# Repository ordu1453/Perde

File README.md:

# Perde

## Repository Layout

| Directory | Contents |
|---|---|
| `hw/` | Hardware design sources (KiCad projects) |
| `fw/` | Firmware sources |
| `mech/` | Mechanical design sources |

## Hardware

The PCB design lives in [`hw/main-board`](hw/main-board), a KiCad 10 project consisting of the schematic (`main-board.kicad_sch`), the board layout (`main-board.kicad_pcb`), and the build configuration for [KiBot](https://github.com/INTI-CMNB/KiBot) (`main-board.kibot.yaml`).

### Continuous Integration / Continuous Delivery

Every change to the hardware design is automatically validated and built by GitHub Actions. The pipeline is implemented with KiBot, executed inside the official `kicad10_auto` / `kicad10_auto_full` container images (KiCad 10), and performs visual revision comparison via [KiDiff](https://github.com/INTI-CMNB/KiDiff), exposed through KiBot's `diff` output. Workflow definitions reside under [`.github/workflows`](.github/workflows).

#### `kicad-ci.yml` — Continuous Integration

Triggered on every push and pull request affecting `hw/main-board/**`. The workflow consists of the following jobs:

| Job | Description |
|---|---|
| **ERC / DRC + docs** | Executes the Electrical Rules Check and Design Rules Check preflights, and generates PDF exports of the schematic and PCB layout. |
| **Gerbers / drill / BOM / STEP** | Produces Gerber and drill files for JLCPCB and PCBWay using KiBot's built-in per-manufacturer templates, each in its own directory with its own ZIP archive (JLCPCB's additionally includes an LCSC-formatted BOM and pick-and-place file); a manufacturer-neutral Bill of Materials (HTML and CSV), a pick-and-place file, and a STEP 3D model are generated separately. |
| **3D renders** | Renders top and bottom views of the assembled board. |
| **Visual diff (KiDiff)** | Generates a red/green visual comparison of the PCB and schematic against a prior revision — the pull request base branch when run on a pull request, or the preceding commit when run on a direct push. |
| **Publish latest build** | Consolidates the outputs of the jobs above, regenerates an interactive KiCanvas schematic/PCB viewer and a KiBot `navigate_results` index over the merged tree, and publishes the result to the `gh-pages` branch under `/latest/`, providing a persistent, browsable link to the most recent build of `main`. |

As the hardware design is presently at an early stage, the pipeline defaults to not failing on design-rule violations: KiBot is invoked with `-D` (`--dont-stop`), which always applies, and each step's `continue-on-error` is controlled by the **`KICAD_CI_STRICT`** repository variable (*Settings → Secrets and variables → Actions → Variables*):

- Unset, or any value other than `true` (default) — lenient: a real ERC/DRC/output failure is still reported in the uploaded artifacts, but does not fail the job, so an early-stage or placeholder design doesn't block CI.
- `true` — strict: a real failure fails the job for real, and any job depending on it (fabrication, renders, publish-latest) is skipped, exactly as with any other genuine CI failure.

Setting `KICAD_CI_STRICT=true` once the design is no longer a placeholder is recommended so a broken board or schematic is reflected honestly in the pipeline's status.

#### `kicad-release.yml` — Release Packaging

Triggered by pushing a tag matching the pattern `vX.Y.Z`. Builds the complete set of documentation, fabrication, assembly, and 3D outputs, and attaches the resulting package to a corresponding GitHub Release. A manual invocation (`workflow_dispatch`) performs the build step only, as no tag is available to publish a release against.

#### Build Outputs

Generated files are retained as downloadable artifacts on each workflow run. In addition, the latest successful build of `main` is published at:

<https://ordu1453.github.io/Perde/latest/>

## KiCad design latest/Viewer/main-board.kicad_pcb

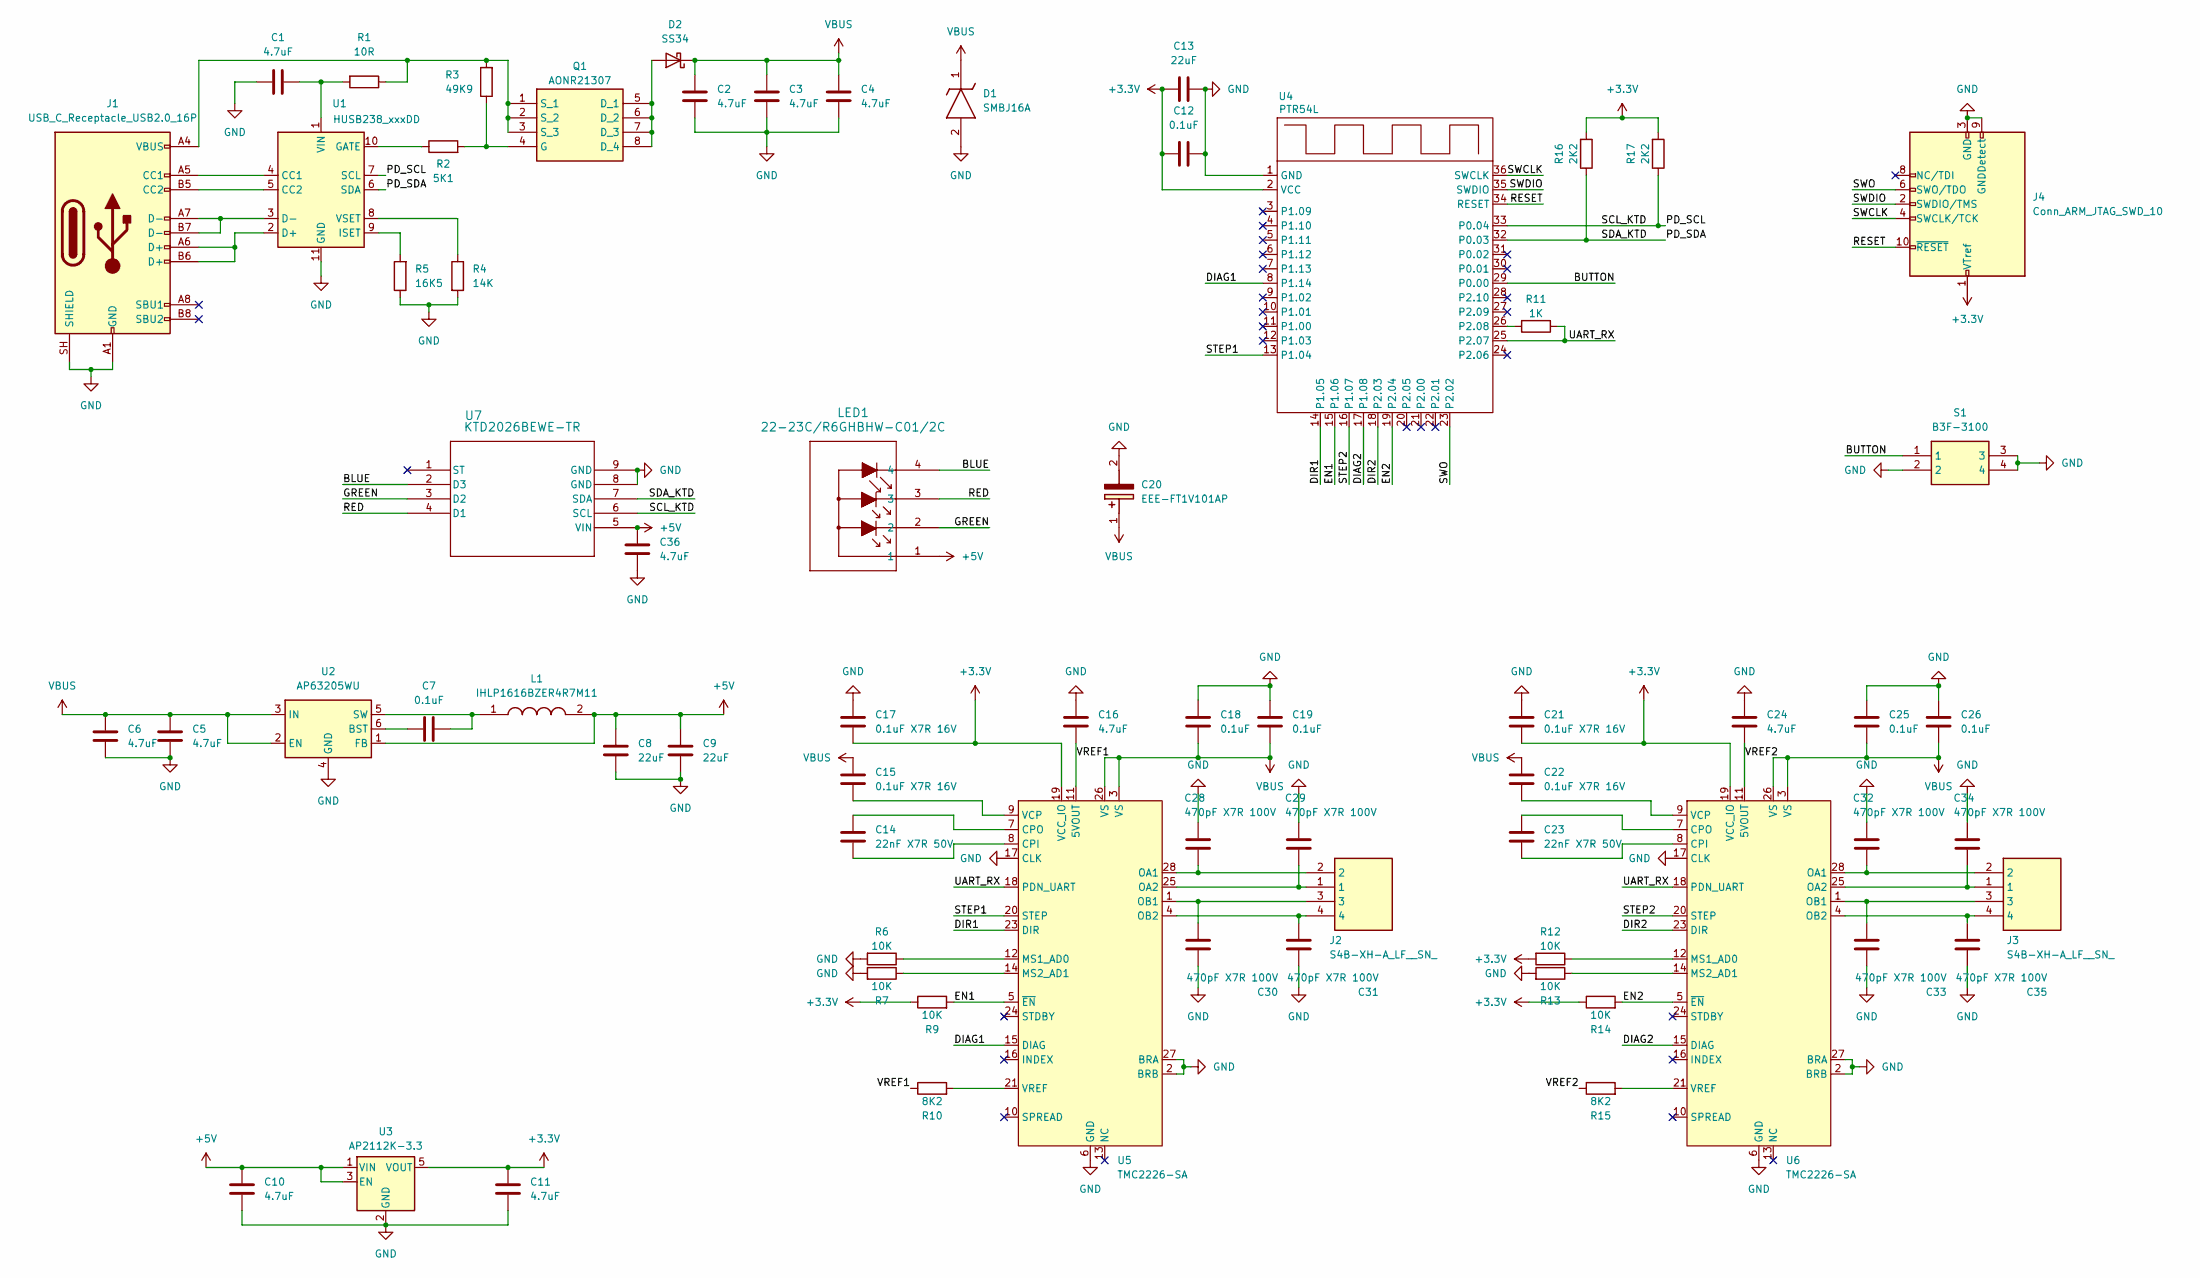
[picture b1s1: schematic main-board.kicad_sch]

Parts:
C1, C2, C3, C4, C5, C6, C10, C11, C16, C24, C36: 4.7uF; C_0805_2012Metric_Pad1.18x1.45mm_HandSolder
C7, C12, C18, C19, C25, C26: 0.1uF; C_0805_2012Metric_Pad1.18x1.45mm_HandSolder
C8, C9, C13: 22uF; C_0603_1608Metric_Pad1.08x0.95mm_HandSolder
C14, C23: 22nF X7R 50V; C_0603_1608Metric_Pad1.08x0.95mm_HandSolder
C15, C17, C21, C22: 0.1uF X7R 16V; C_0603_1608Metric_Pad1.08x0.95mm_HandSolder
C20: EEE-FT1V101AP; EEE1AA101SP; Manufacturer_Part_Number EEE-FT1V101AP; Mouser Part Number 667-EEE-FT1V101AP
C28, C29, C30, C31, C32, C33, C34, C35: 470pF X7R 100V; C_0805_2012Metric_Pad1.18x1.45mm_HandSolder
D1: SMBJ16A; DIOM5436X261N; Manufacturer_Part_Number SMBJ16A; Mouser Part Number 576-SMBJ16A
D2: SS34; D_SMA
J1: USB_C_Receptacle_USB2.0_16P; USB_C_Receptacle_Palconn_UTC16-G
J2, J3: S4B-XH-A_LF__SN_; S4BXHALFSN; Manufacturer_Part_Number S4B-XH-A(LF)(SN); Mouser Part Number N/A
J4: Conn_ARM_JTAG_SWD_10; PinHeader_2x05_P1.27mm_Vertical_SMD
L1: IHLP1616BZER4R7M11; INDPM4441X200N; Manufacturer_Part_Number IHLP1616BZER4R7M11; Mouser Part Number 70-IHLP1616BZER4R7M1
LED1: 22-23C/R6GHBHW-C01/2C; 22-23C_EVE
Q1: AONR21307; DFN_3X3_EP; Manufacturer_Part_Number AONR21307
R1: 10R; R_0805_2012Metric_Pad1.20x1.40mm_HandSolder
R2: 5K1; R_0805_2012Metric_Pad1.20x1.40mm_HandSolder
R3: 49K9; R_0805_2012Metric_Pad1.20x1.40mm_HandSolder
R4: 14K; R_0603_1608Metric_Pad0.98x0.95mm_HandSolder
R5: 16K5; R_0603_1608Metric_Pad0.98x0.95mm_HandSolder
R6, R7, R9, R12, R13, R14: 10K; R_0603_1608Metric_Pad0.98x0.95mm_HandSolder
R10, R15: 8K2; R_0603_1608Metric_Pad0.98x0.95mm_HandSolder
R11: 1K; R_0603_1608Metric_Pad0.98x0.95mm_HandSolder
R16, R17: 2K2; R_0603_1608Metric_Pad0.98x0.95mm_HandSolder
S1: B3F-3100; B3F3100; Manufacturer_Part_Number B3F-3100; Mouser Part Number 653-B3F-3100
U1: HUSB238_xxxDD; WDFN-10-1EP_3x3mm_P0.5mm_EP1.8x2.5mm
U2: AP63205WU; TSOT-23-6
U3: AP2112K-3.3; SOT-23-5
U4: PTR54L; PTR54L15
U5, U6: TMC2226-SA; HTSSOP-28-1EP_4.4x9.7mm_P0.65mm_EP2.75x6.2mm_ThermalVias
U7: KTD2026BEWE-TR; UTDFN8_1P5X1P5_KIN

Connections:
+3.3V: C11.1, C12.2, C13.2, C17.2, C21.2, J4.1 (VTref), R9.1, R12.2, R14.1, R16.2, R17.2, U3.5 (VOUT), U4.2 (VCC), U5.19 (VCC_IO), U6.19 (VCC_IO)
+5V: C8.2, C9.2, C10.1, C36.1, L1.2, LED1.1, U2.1 (FB), U3.1 (VIN), U3.3 (EN), U7.5 (VIN)
/BLUE: LED1.4, U7.2 (D3)
/BUTTON: S1.1, U4.29 (P0.00)
/DIAG1: U4.8 (P1.14), U5.15 (DIAG)
/DIAG2: U4.17 (P1.08), U6.15 (DIAG)
/DIR1: U4.14 (P1.05), U5.23 (DIR)
/DIR2: U4.18 (P2.03), U6.23 (DIR)
/EN1: R9.2, U4.15 (P1.06), U5.5 (~EN)
/EN2: R14.2, U4.19 (P2.04), U6.5 (~EN)
/GREEN: LED1.2, U7.3 (D2)
/PD_SCL: R17.1, U1.7 (SCL), U4.33 (P0.04), U7.6 (SCL)
/PD_SDA: R16.1, U1.6 (SDA), U4.32 (P0.03), U7.7 (SDA)
/RED: LED1.3, U7.4 (D1)
/RESET: J4.10 (~RESET), U4.34 (RESET)
/STEP1: U4.13 (P1.04), U5.20 (STEP)
/STEP2: U4.16 (P1.07), U6.20 (STEP)
/SWCLK: J4.4 (SWCLK/TCK), U4.36 (SWCLK)
/SWDIO: J4.2 (SWDIO/TMS), U4.35 (SWDIO)
/SWO: J4.6 (SWO/TDO), U4.23 (P2.02)
/UART_RX: R11.1, U4.25 (P2.07), U5.18 (PDN_UART), U6.18 (PDN_UART)
/VREF1: C16.2, R10.1, U5.11 (5VOUT)
/VREF2: C24.2, R15.1, U6.11 (5VOUT)
GND: C1.1, C2.2, C3.2, C4.2, C5.2, C6.2, C8.1, C9.1, C10.2, C11.2, C12.1, C13.1, C16.1, C17.1, C18.1, C19.1, C20.2 (-), C21.1, C24.1, C25.1, C26.1, C28.1, C29.1, C30.1, C31.1, C32.1, C33.1, C34.1, C35.1, C36.2, D1.2 (A), J1.A1 (GND), J1.A12 (GND), J1.B1 (GND), J1.B12 (GND), J1.SH (SHIELD), J4.3 (GND), J4.5 (GND), J4.9 (GNDDetect), R4.2, R5.1, R6.2, R7.2, R13.2, S1.2, S1.3, S1.4, U1.11 (GND), U2.4 (GND), U3.2 (GND), U4.1 (GND), U5.2 (BRB), U5.6 (GND), U5.17 (CLK), U5.22 (GND), U5.27 (BRA), U5.29 (GND), U6.2 (BRB), U6.6 (GND), U6.17 (CLK), U6.22 (GND), U6.27 (BRA), U6.29 (GND), U7.8 (GND), U7.9 (GND)
unnamed: D2.2 (A), Q1.5 (D_1), Q1.6 (D_2), Q1.7 (D_3), Q1.8 (D_4)
unnamed: J1.A5 (CC1), U1.4 (CC1)
unnamed: J1.B5 (CC2), U1.5 (CC2)
unnamed: Q1.4 (G), R2.2, R3.1
unnamed: J1.A4 (VBUS), J1.A9 (VBUS), J1.B4 (VBUS), J1.B9 (VBUS), Q1.1 (S_1), Q1.2 (S_2), Q1.3 (S_3), R1.1, R3.2
unnamed: J1.A6 (D+), J1.B6 (D+), U1.2 (D+)
unnamed: J1.A7 (D-), J1.B7 (D-), U1.3 (D-)
unnamed: R2.1, U1.10 (GATE)
unnamed: R5.2, U1.9 (ISET)
unnamed: C1.2, R1.2, U1.1 (VIN)
unnamed: R4.1, U1.8 (VSET)
unnamed: C7.1, U2.6 (BST)
unnamed: C7.2, L1.1, U2.5 (SW)
unnamed: R11.2, U4.26 (P2.08)
unnamed: C14.1, U5.8 (CPI)
unnamed: C14.2, U5.7 (CPO)
unnamed: R6.1, U5.12 (MS1_AD0)
unnamed: R7.1, U5.14 (MS2_AD1)
unnamed: C28.2, J2.2, U5.28 (OA1)
unnamed: C29.2, J2.1, U5.25 (OA2)
unnamed: C30.2, J2.3, U5.1 (OB1)
unnamed: C31.2, J2.4, U5.4 (OB2)
unnamed: C15.2, U5.9 (VCP)
unnamed: R10.2, U5.21 (VREF)
unnamed: C23.1, U6.8 (CPI)
unnamed: C23.2, U6.7 (CPO)
unnamed: R12.1, U6.12 (MS1_AD0)
unnamed: R13.1, U6.14 (MS2_AD1)
unnamed: C32.2, J3.2, U6.28 (OA1)
unnamed: C34.2, J3.1, U6.25 (OA2)
unnamed: C33.2, J3.3, U6.1 (OB1)
unnamed: C35.2, J3.4, U6.4 (OB2)
unnamed: C22.2, U6.9 (VCP)
unnamed: R15.2, U6.21 (VREF)
VBUS: C2.1, C3.1, C4.1, C5.1, C6.1, C15.1, C18.2, C19.2, C20.1 (+), C22.1, C25.2, C26.2, D1.1 (K), D2.1 (K), U2.2 (EN), U2.3 (IN), U5.3 (VS), U5.26 (VS), U6.3 (VS), U6.26 (VS)

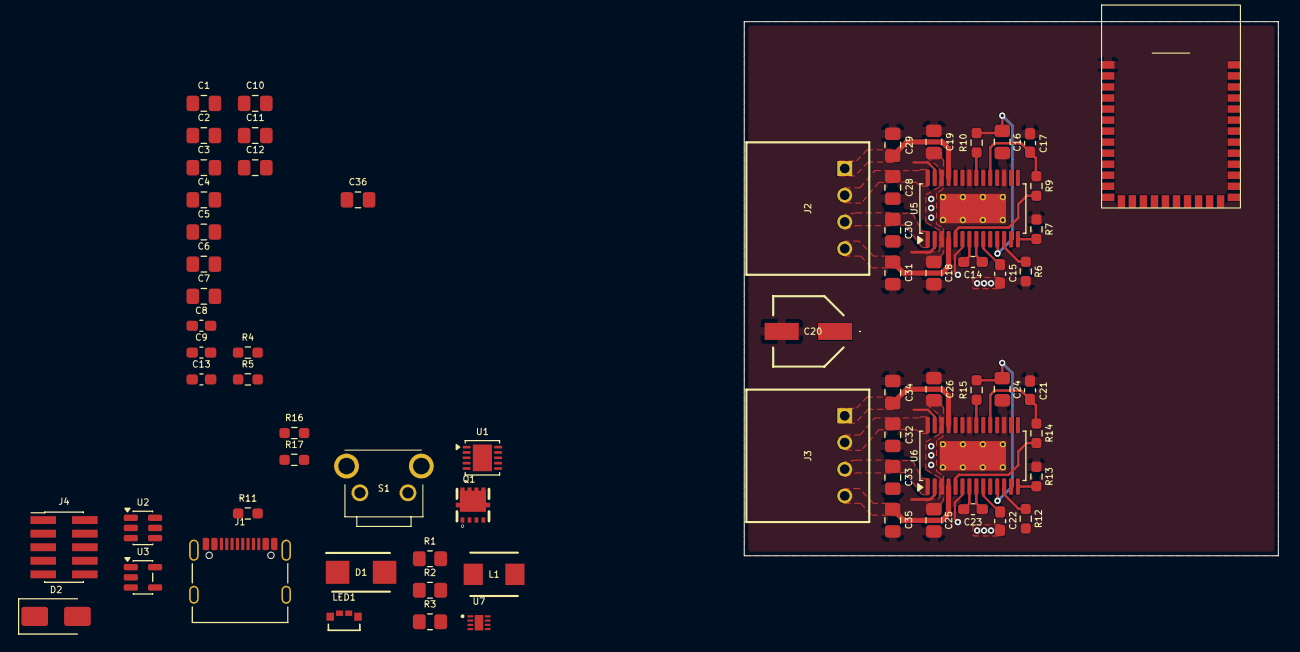
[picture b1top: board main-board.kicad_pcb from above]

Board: 4 copper layers, 50.0 x 50.0 mm, 68 parts (0 on the bottom side), 59 nets.

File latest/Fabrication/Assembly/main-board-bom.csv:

Row,Description,Part,References,Value,Footprint,Quantity Per PCB,Status,Datasheet,Height,Manufacturer_Name,Manufacturer_Part_Number,Mouser Part Number,Mouser Price/Stock,Arrow Part Number,Arrow Price/Stock
1,Unpolarized capacitor,C,C28 C29 C30 C31 C32 C33 C34 C35,470 pF,C_0805_2012Metric_Pad1.18x1.45mm_HandSolder,8, ,,,,,,,,
2,Unpolarized capacitor,C,C14 C23,22 nF,C_0603_1608Metric_Pad1.08x0.95mm_HandSolder,2, ,,,,,,,,
3,Unpolarized capacitor,C,C7 C12 C18 C19 C25 C26,100 nF,C_0805_2012Metric_Pad1.18x1.45mm_HandSolder,6, ,,,,,,,,
4,Unpolarized capacitor,C,C15 C17 C21 C22,100 nF,C_0603_1608Metric_Pad1.08x0.95mm_HandSolder,4, ,,,,,,,,
5,Unpolarized capacitor,C,C1 C2 C3 C4 C5 C6 C10 C11 C16 C24 C36,4.7 µF,C_0805_2012Metric_Pad1.18x1.45mm_HandSolder,11, ,,,,,,,,
6,Unpolarized capacitor,C,C8 C9 C13,22 µF,C_0603_1608Metric_Pad1.08x0.95mm_HandSolder,3, ,,,,,,,,
7,Aluminum Electrolytic Capacitors - SMD 100uF 35volts 6.3x5.8mm SMD,EEE-FT1V101AP,C20,EEE-FT1V101AP,EEE1AA101SP,1, ,http://industrial.panasonic.com/cdbs/www-data/pdf/RDE0000/AB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,7.8,Panasonic,EEE-FT1V101AP,667-EEE-FT1V101AP,https://www.mouser.co.uk/ProductDetail/Panasonic/EEE-FT1V101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,EEE-FT1V101AP,https://www.arrow.com/en/products/eeeft1v101ap/panasonic.htm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
8,TVS Diode Single Uni-Dir 16V 600W 2-Pin SMB T/R,SMBJ16A,D1,SMBJ16A,DIOM5436X261N,1, ,https://datasheet.datasheetarchive.com/originals/dk/DKDS-14/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,2.61,LITTELFUSE,SMBJ16A,576-SMBJ16A,https://www.mouser.co.uk/ProductDetail/Littelfuse/SMBJ16A?qs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,SMBJ16A,https://www.arrow.com/en/products/smbj16a/littelfuse?utm_cur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
9,"40V 3A Schottky Diode, SMA",SS34,D2,SS34,D_SMA,1, ,https://www.vishay.com/docs/88751/ss32.pdf,,,,,,,
10,"Cortex Debug Connector, standard ARM Cortex-M SWD and JTAG interface",Conn_ARM_JTAG_SWD_10,J4,Conn_ARM_JTAG_SWD_10,PinHeader_2x05_P1.27mm_Vertical_SMD,1, ,http://infocenter.arm.com/help/topic/com.arm.doc.ddi0314h/DD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,,,,,,,
11,"XH-2.5mm Header side entry 4 way JST XH Series, Series Number S4B, 2.5mm Pitch 4 Way 1 Row Right Angle PCB Header, Solder Termination, 3A",S4B-XH-A_LF__SN_,J2 J3,S4B-XH-A_LF__SN_,S4BXHALFSN,2, ,https://www.mouser.co.uk/ProductDetail/JST-Commercial/S4B-XH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,7,JST (JAPAN SOLDERLESS TERMINALS),S4B-XH-A(LF)(SN),N/A,https://www.mouser.co.uk/ProductDetail/JST-Commercial/S4B-XH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,S4B-XH-A(LF)(SN),https://www.arrow.com/en/products/s4b-xh-a-lf-sn/jst-manufac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
12,USB 2.0-only 16P Type-C Receptacle connector,USB_C_Receptacle_USB2.0_16P,J1,USB_C_Receptacle_USB2.0_16P,USB_C_Receptacle_Palconn_UTC16-G,1, ,https://www.usb.org/sites/default/files/documents/usb_type-c.zip,,,,,,,
13,Vishay IHLP1616BZ-11 Series Shielded Wire-wound SMD Inductor 4.7 uH +/-20% 1.75A Idc,IHLP1616BZER4R7M11,L1,IHLP1616BZER4R7M11,INDPM4441X200N,1, ,https://www.vishay.com/docs/34196/lp16bz11.pdf,2,Vishay,IHLP1616BZER4R7M11,70-IHLP1616BZER4R7M1,https://www.mouser.co.uk/ProductDetail/Vishay-Dale/IHLP1616B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,IHLP1616BZER4R7M11,https://www.arrow.com/en/products/ihlp1616bzer4r7m11/vishay
14,,22-23C_R6GHBHW-C01_2C,LED1,22-23C/R6GHBHW-C01/2C,22-23C_EVE,1, ,22-23C/R6GHBHW-C01/2C,,,,,,,
15,30V P-Channel MOSFET,AONR21307,Q1,AONR21307,DFN_3X3_EP,1, ,http://www.aosmd.com/pdfs/datasheet/AONR21307.pdf,,Alpha & Omega Semiconductors,AONR21307,,,AONR21307,https://www.arrow.com/en/products/aonr21307/alpha-and-omega-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
16,Resistor,R,R1,10 Ω,R_0805_2012Metric_Pad1.20x1.40mm_HandSolder,1, ,,,,,,,,
17,Resistor,R,R11,1 kΩ,R_0603_1608Metric_Pad0.98x0.95mm_HandSolder,1, ,,,,,,,,
18,Resistor,R,R16 R17,2.2 kΩ,R_0603_1608Metric_Pad0.98x0.95mm_HandSolder,2, ,,,,,,,,
19,Resistor,R,R2,5.1 kΩ,R_0805_2012Metric_Pad1.20x1.40mm_HandSolder,1, ,,,,,,,,
20,Resistor,R,R10 R15,8.2 kΩ,R_0603_1608Metric_Pad0.98x0.95mm_HandSolder,2, ,,,,,,,,
21,Resistor,R,R6 R7 R9 R12 R13 R14,10 kΩ,R_0603_1608Metric_Pad0.98x0.95mm_HandSolder,6, ,,,,,,,,
22,Resistor,R,R4,14 kΩ,R_0603_1608Metric_Pad0.98x0.95mm_HandSolder,1, ,,,,,,,,
23,Resistor,R,R5,16.5 kΩ,R_0603_1608Metric_Pad0.98x0.95mm_HandSolder,1, ,,,,,,,,
24,Resistor,R,R3,49.9 kΩ,R_0805_2012Metric_Pad1.20x1.40mm_HandSolder,1, ,,,,,,,,
25,"Grey Plunger Tactile Switch, SPST-NO 50 mA @ 24 V dc 0.9mm",B3F-3100,S1,B3F-3100,B3F3100,1, ,http://omronfs.omron.com/en_US/ecb/products/pdf/en-b3f.pdf,7,OMRON Electronics,B3F-3100,653-B3F-3100,https://www.mouser.co.uk/ProductDetail/Omron-Electronics/B3F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,B3F-3100,https://www.arrow.com/en/products/b3f3100/omron.html?utm_cur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
26,"600mA low dropout linear regulator, with enable pin, 3.8V-6V input voltage range, 3.3V fixed positive output, SOT-23-5",AP2112K-3.3,U3,AP2112K-3.3,SOT-23-5,1, ,https://www.diodes.com/assets/Datasheets/AP2112.pdf,,,,,,,
27,"2A, 1.1MHz Buck DC/DC Converter, fixed 5.0V output voltage, TSOT-23-6",AP63205WU,U2,AP63205WU,TSOT-23-6,1, ,https://www.diodes.com/assets/Datasheets/AP63200-AP63201-AP6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,,,,,,,
28,"USB-PD Sink IC Port Controller, VBUS = 3..25V, USB Type-C rev. 1.4, USB-PD rev. 3.0, BC1.2, WDFN-10 / WSON-10",HUSB238_xxxDD,U1,HUSB238_xxxDD,WDFN-10-1EP_3x3mm_P0.5mm_EP1.8x2.5mm,1, ,https://cdn-learn.adafruit.com/assets/assets/000/125/150/ori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,,,,,,,
29,,KTD2026BEWE-TR,U7,KTD2026BEWE-TR,UTDFN8_1P5X1P5_KIN,1, ,KTD2026BEWE-TR,,,,,,,
30,,PTR54L,U4,PTR54L,PTR54L15,1, ,,,,,,,,
31,"Power Driver For Stepper Motors, 2.0A, 4.75-29V, HTSSOP-28",TMC2226-SA,U5 U6,TMC2226-SA,HTSSOP-28-1EP_4.4x9.7mm_P0.65mm_EP2.75x6.2mm_ThermalVias,2, ,https://www.trinamic.com/fileadmin/assets/Products/ICs_Docum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,,,,,,,





Project info:
Schematic:,main-board
Variant:,default
Revision:,${REVISION}
Date:,2026-09-26_19-41-47
KiCad Version:,10.0.4-10.0.4~ubuntu25.10.1
Statistics:
Component Groups:,31
Component Count:,68
Fitted Components:,68
Number of PCBs:,1
Total Components:,68
